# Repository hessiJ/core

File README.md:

core
========================================

A feather wing shield with ADC and highG ACC.

Repository Contents
-------------------

* **/Hardware** - Eagle design files (.brd, .sch)
* **/Firmware** - Contains the library for the microcontroller (.h, .cpp)
* **/Software** - Contains the apk library for android 

Documentation
--------------

Product Versions Hardware
----------------
* [core-feather-shield-adc-hGacc] - A feather wing shield with ADC and highG ACC.
* [core-feather-shield-adc-imu-basic_v1_0] - A feather wing shield with ADC and IMU.
* [core-feather-shield-adc-imu-basic_v2_0] - A feather wing shield with ADC and IMU.
* [core-feather-shield-adc-imu-advanced_v1_0] - A feather wing shield with multi-channel ADC and IMU.
* [core-feather-shield-adc-imu-advanced_v1_1] - A feather wing shield with multi-channel ADC and IMU.

Version History
---------------
* [V1.0.0] - Initial Release

License Information
-------------------

This product is _**open source**_! 

Please review the LICENSE.md file for license information. 

Distributed as-is; no warranty is given.

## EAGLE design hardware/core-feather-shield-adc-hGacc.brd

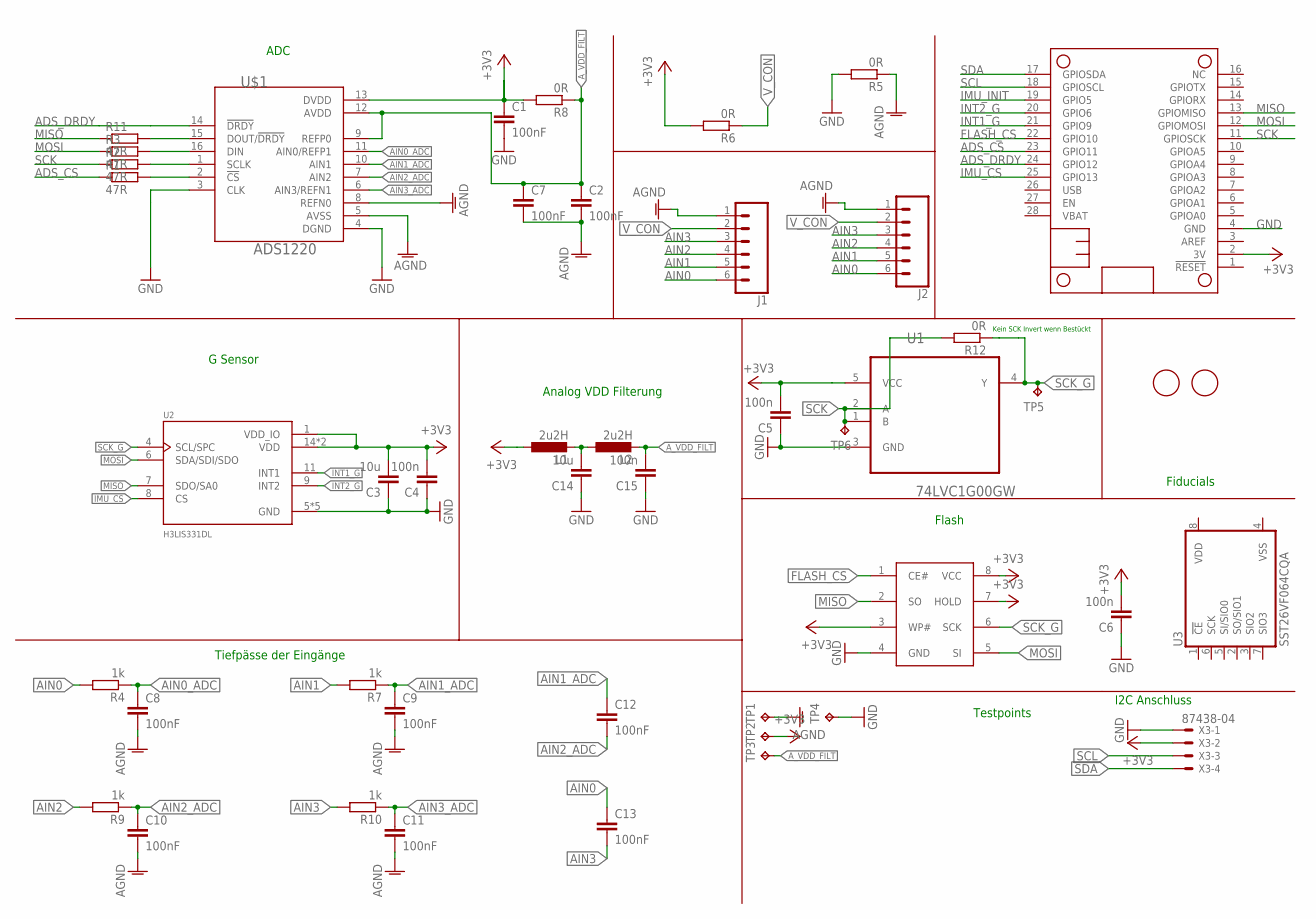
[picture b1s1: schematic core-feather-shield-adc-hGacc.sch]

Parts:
C1, C2, C7, C8, C9, C10, C11, C12, C13: 100nF; C0805
C3, C14: 10u; C0805
C4, C5, C6, C15: 100n; C0805
J1, J2: CONN_06SMD_MALE; 1X06_SMD_MALE
L1, L2: 2u2H; L0805
MS1: FEATHERWING
R1, R2, R3, R11: 47R; R0805
R4, R7, R9, R10: 1k; R0805
R5, R6, R8, R12: 0R; R0805
TP1, TP2, TP3, TP4, TP5, TP6: TPTP10R; TP10R
U1: 74LVC1G00GW; SOT65P210X110-5N
U2: H3LIS331DL; QFN300X300X100-16N
U3: SST26VF064CQA; WSON8
U$1: ADS1220; TSSOP-16
U$2: IS25LP128F-JKLE-TR; WSON-8-PAD
U$8, U$9: FIDUCIAL; FIDUCIAL_1MM
X3: 87438-04

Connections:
+3V3: C1.1, C3.2, C4.2, C5.2, C6.2, L1.1, MS1.2 (3V), R6.2, R8.2, TP2.TP, U1.5 (VCC), U2.1 (VDD_IO), U2.14 (VDD), U2.15 (VDD), U$1.13 (DVDD), U$2.3 (WP#), U$2.7 (HOLD), U$2.8 (VCC), X3.2
ADS_CS: MS1.23 (GPIO11), R1.1
ADS_DRDY: MS1.24 (GPIO12), U$1.14 (!DRDY)
AGND: C2.2, C7.2, C8.2, C9.2, C10.2, C11.2, J1.1, J2.1, R5.1, TP1.TP, U$1.5 (AVSS), U$1.8 (REFN0)
AIN0: C13.1, J1.6, J2.6, R4.2
AIN0_ADC: C8.1, R4.1, U$1.11 (AIN0/REFP1)
AIN1: J1.5, J2.5, R7.2
AIN1_ADC: C9.1, C12.1, R7.1, U$1.10 (AIN1)
AIN2: J1.4, J2.4, R9.2
AIN2_ADC: C10.1, C12.2, R9.1, U$1.7 (AIN2)
AIN3: C13.2, J1.3, J2.3, R10.2
AIN3_ADC: C11.1, R10.1, U$1.6 (AIN3/REFN1)
A_VDD_FILT: C2.1, C7.1, C15.2, L2.2, R8.1, TP3.TP, U$1.9 (REFP0), U$1.12 (AVDD)
FLASH_CS: MS1.22 (GPIO10), U$2.1 (CE#)
GND: C1.2, C3.1, C4.1, C5.1, C6.1, C14.1, C15.1, MS1.4 (GND), R5.2, TP4.TP, U1.3 (GND), U2.5 (GND), U2.10 (GND), U2.12 (GND), U2.13 (GND), U2.16 (GND), U$1.4 (DGND), U$2.4 (GND), X3.1
IMU_CS: MS1.25 (GPIO13), U2.8 (CS)
IMU_INIT: MS1.19 (GPIO5)
INT1_G: MS1.21 (GPIO9), U2.11 (INT1)
INT2_G: MS1.20 (GPIO6), U2.9 (INT2)
MISO: MS1.13 (GPIOMISO), R11.1, U2.7 (SDO/SA0), U$2.2 (SO)
MOSI: MS1.12 (GPIOMOSI), R3.1, U2.6 (SDA/SDI/SDO), U$2.5 (SI)
unnamed: R11.2, U$1.15 (DOUT/!DRDY)
unnamed: C14.2, L1.2, L2.1
unnamed: R3.2, U$1.16 (DIN)
unnamed: R2.2, U$1.1 (SCLK)
unnamed: R1.2, U$1.2 (!CS)
SCK: MS1.11 (GPIOSCK), R2.1, R12.2, TP6.TP, U1.1 (B), U1.2 (A)
SCK_G: R12.1, TP5.TP, U1.4 (Y), U2.4 (SCL/SPC), U$2.6 (SCK)
SCL: MS1.18 (GPIOSCL), X3.3
SDA: MS1.17 (GPIOSDA), X3.4
VDD: U3.8 (VDD)
VSS: U3.4 (VSS)
V_CON: J1.2, J2.2, R6.1

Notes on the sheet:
Fiducials
Kein SCK Invert wenn Bestückt
Flash
I2C Anschluss
Tiefpässe der Eingänge
G Sensor
Analog VDD Filterung
ADC
Testpoints

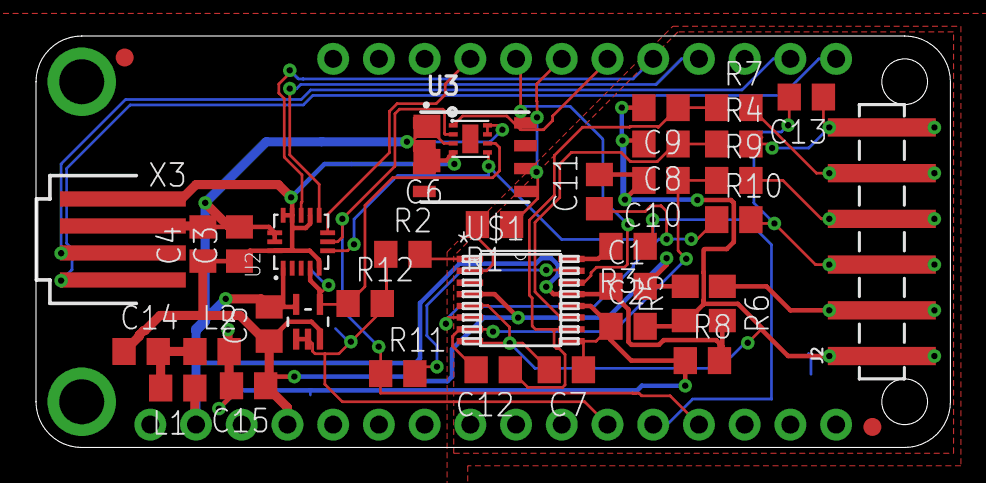
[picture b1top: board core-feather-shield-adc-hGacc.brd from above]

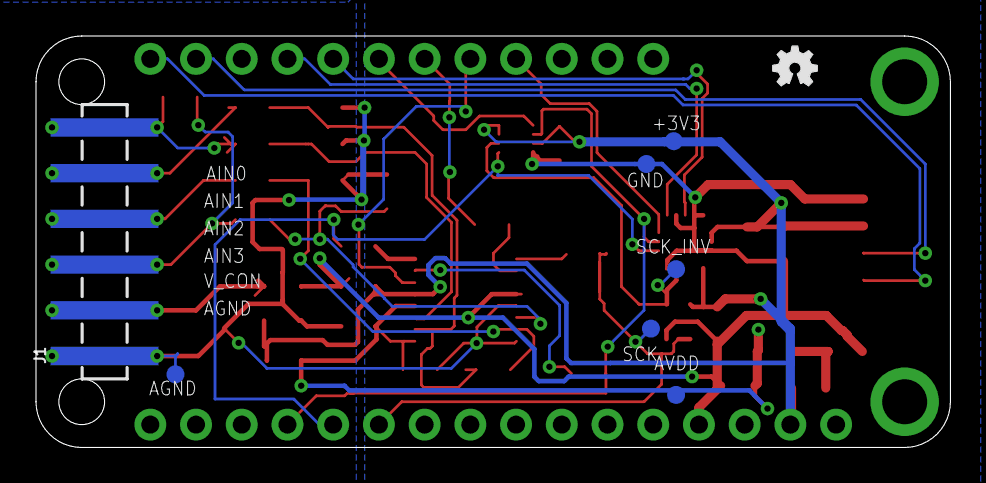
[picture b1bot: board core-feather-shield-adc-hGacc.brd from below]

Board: 2 copper layers, 50.8 x 22.9 mm, 49 parts (8 on the bottom side), 30 nets.

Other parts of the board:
FRAME2: FRAME-LETTER; CREATIVE_COMMONS
LOGO1: OSHW-LOGOMINI; OSHW-LOGO-MINI
LOGO2: REVISION

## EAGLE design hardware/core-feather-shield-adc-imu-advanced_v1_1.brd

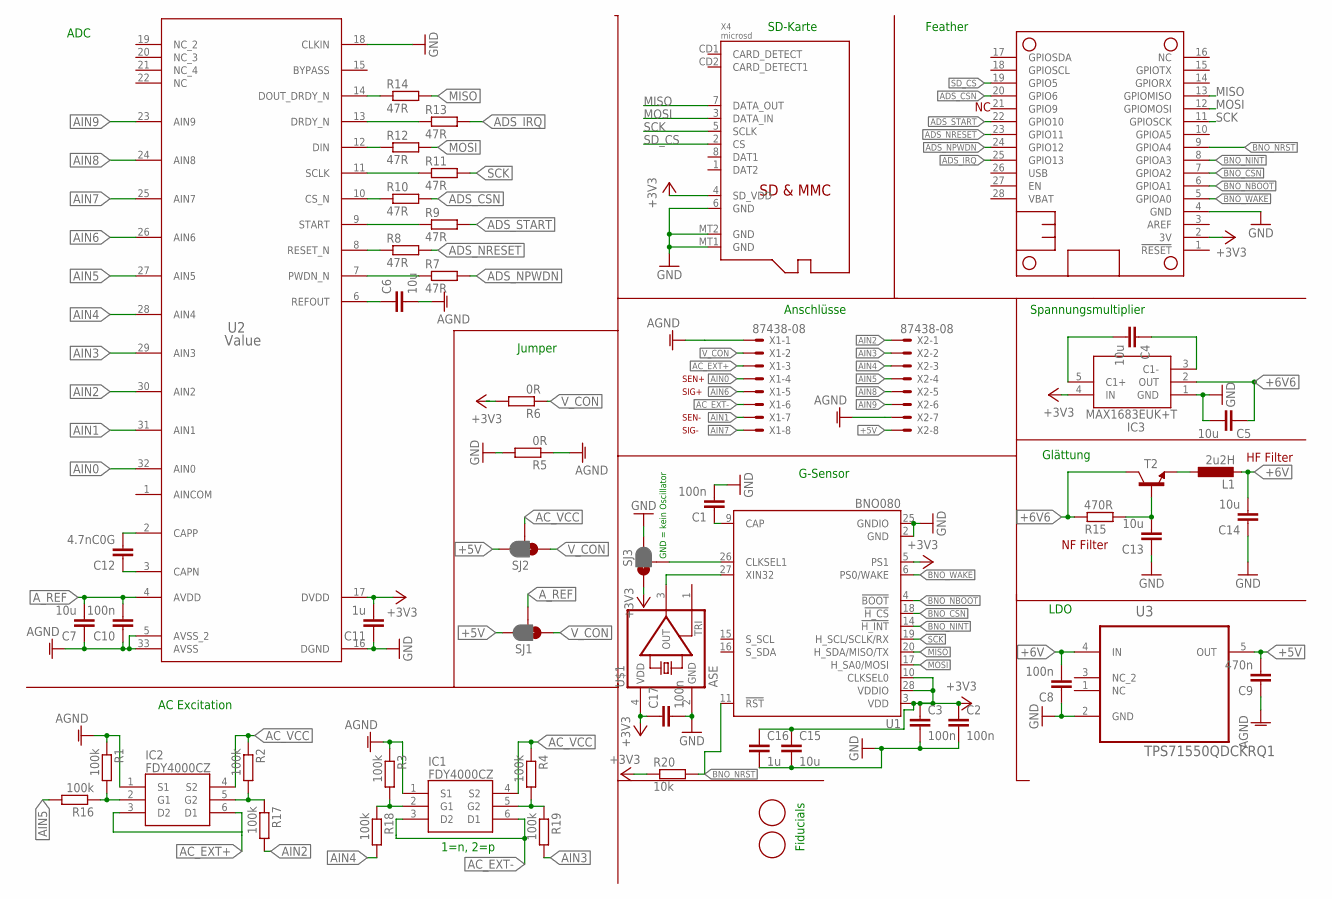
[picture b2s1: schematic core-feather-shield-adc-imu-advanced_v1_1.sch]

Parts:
C1, C2, C3, C8, C10, C17: 100n; C0805
C4, C5, C6, C7, C13, C14, C15: 10u; C0805
C9: 470n; C0805
C11, C16: 1u; C0805
C12: 4.7nC0G; C0805
IC1, IC2: FDY4000CZ; SOTFL50P160X60-6N
IC3: MAX1683EUK+T; SOT95P280X145-5N
L1: 2u2H; L0805
MS1: FEATHERWING
R1, R2, R3, R4, R16, R17, R18, R19: 100k; R0805
R5, R6: 0R; R0805
R7, R8, R9, R10, R11, R12, R13, R14: 47R; R0805
R15: 470R; R0805
R20: 10k; R0805
SJ1, SJ2, SJ3: JUMPER_PAD-3-1&2_NC_BY_PASTE; PAD-HUMPER-3-1&2_NC_BY_PASTE_YES_SILK_FULL_BOX
T2: BC808-NPN-SOT23-BEC; SOT23-BEC
U1: BNO080; LGA-28
U2: Value; RHB0032E
U3: TPS71550QDCKRQ1; SOT65P210X110-5N
U$1: ASE
U$8, U$9: FIDUCIAL; FIDUCIAL_1MM
X1, X2: 87438-08
X4: microsd; MICROSD

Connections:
+3V3: C2.1, C3.1, C11.2, C15.1, C16.1, C17.1, IC3.4 (IN), MS1.2 (3V), R6.2, R20.1, SJ3.3, U1.3 (VDD), U1.5 (PS1), U1.10 (CLKSEL0), U1.28 (VDDIO), U2.17 (DVDD), U$1.4 (VDD), X4.4 (SD_VDD)
+5V: C9.2, SJ1.1, SJ2.1, U3.5 (OUT), X2.8
+6V: C8.2, C14.2, L1.2, U3.4 (IN)
+6V6: C5.1, IC3.2 (OUT), R15.2, T2.C
AC_EXT+: IC2.3 (D2), IC2.6 (D1), X1.3
AC_EXT-: IC1.3 (D2), IC1.6 (D1), X1.6
AC_VCC: IC1.4 (S2), IC2.4 (S2), R2.1, R4.1, SJ2.2
ADS_CSN: MS1.20 (GPIO6), R10.2
ADS_IRQ: MS1.25 (GPIO13), R13.2
ADS_NPWDN: MS1.24 (GPIO12), R7.2
ADS_NRESET: MS1.23 (GPIO11), R8.2
ADS_START: MS1.22 (GPIO10), R9.2
AGND: C6.2, C7.1, C9.1, C10.1, IC1.1 (S1), IC2.1 (S1), R1.1, R3.1, R5.1, U2.5 (AVSS_2), U2.33 (AVSS), X1.1, X2.7
AIN0: U2.32 (AIN0), X1.4
AIN1: U2.31 (AIN1), X1.7
AIN2: R17.2, U2.30 (AIN2), X2.1
AIN2_P: IC2.5 (G2), R2.2, R17.1
AIN3: R19.2, U2.29 (AIN3), X2.2
AIN3_P: IC1.5 (G2), R4.2, R19.1
AIN4: R18.2, U2.28 (AIN4), X2.3
AIN4_N: IC1.2 (G1), R3.2, R18.1
AIN5: R16.2, U2.27 (AIN5), X2.4
AIN5_N: IC2.2 (G1), R1.2, R16.1
AIN6: U2.26 (AIN6), X1.5
AIN7: U2.25 (AIN7), X1.8
AIN8: U2.24 (AIN8), X2.5
AIN9: U2.23 (AIN9), X2.6
A_REF: C7.2, C10.2, SJ1.2, U2.4 (AVDD)
BNO_CSN: MS1.7 (GPIOA2), U1.18 (!H_CS)
BNO_NBOOT: MS1.6 (GPIOA1), U1.4 (!BOOT)
BNO_NINT: MS1.8 (GPIOA3), U1.14 (!H_INT)
BNO_NRST: MS1.9 (GPIOA4), R20.2, U1.11 (!RST)
BNO_WAKE: MS1.5 (GPIOA0), U1.6 (PS0/WAKE)
GND: C1.2, C2.2, C3.2, C5.2, C8.1, C11.1, C13.1, C14.1, C15.2, C16.2, C17.2, IC3.1 (GND), MS1.4 (GND), R5.2, SJ3.1, U1.2 (GND), U1.25 (GNDIO), U2.16 (DGND), U2.18 (CLKIN), U3.2 (GND), U$1.2 (GND), X4.6 (GND), X4.MT1 (GND), X4.MT2 (GND)
MISO: MS1.13 (GPIOMISO), R14.2, U1.20 (H_SDA/MISO/TX), X4.7 (DATA_OUT)
MOSI: MS1.12 (GPIOMOSI), R12.2, U1.17 (H_SA0/MOSI), X4.3 (DATA_IN)
unnamed: C1.1, U1.9 (CAP)
unnamed: C4.1, IC3.3 (C1-)
unnamed: C4.2, IC3.5 (C1+)
unnamed: C13.2, R15.1, T2.B
unnamed: L1.1, T2.E
unnamed: C6.1, U2.6 (REFOUT)
unnamed: C12.2, U2.2 (CAPP)
unnamed: C12.1, U2.3 (CAPN)
unnamed: R7.1, U2.7 (PWDN_N)
unnamed: R8.1, U2.8 (RESET_N)
unnamed: R9.1, U2.9 (START)
unnamed: R10.1, U2.10 (CS_N)
unnamed: R11.1, U2.11 (SCLK)
unnamed: R14.1, U2.14 (DOUT_DRDY_N)
unnamed: R13.1, U2.13 (DRDY_N)
unnamed: R12.1, U2.12 (DIN)
unnamed: U1.27 (XIN32), U$1.3 (OUT)
unnamed: SJ3.2, U1.26 (CLKSEL1)
SCK: MS1.11 (GPIOSCK), R11.2, U1.19 (H_SCL/SCLK/RX), X4.5 (SCLK)
SD_CS: MS1.19 (GPIO5), X4.2 (CS)
V_CON: R6.1, SJ1.3, SJ2.3, X1.2

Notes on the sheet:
Fiducials
1=n, 2=p
LDO
Spannungsmultiplier
Glättung
NF Filter
HF Filter
SEN+
SEN-
SIG+
SIG-
G-Sensor
ADC
AC Excitation
Jumper
Anschlüsse
SD-Karte
Feather
GND = kein Oscillator

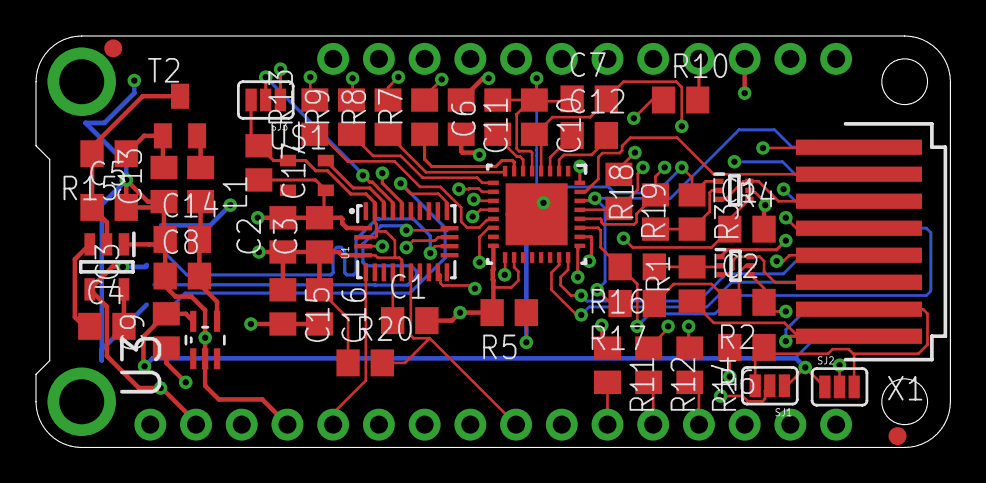
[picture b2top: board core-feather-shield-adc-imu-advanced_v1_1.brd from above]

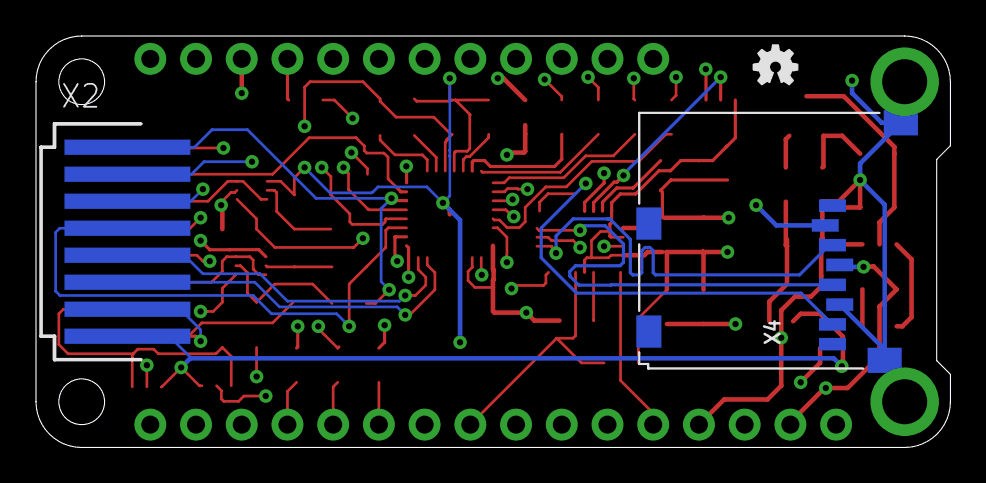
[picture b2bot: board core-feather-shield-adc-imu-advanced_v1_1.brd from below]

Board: 4 copper layers, 50.8 x 22.9 mm, 58 parts (3 on the bottom side), 57 nets.

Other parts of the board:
FRAME2: FRAME-LETTER; CREATIVE_COMMONS
LOGO1: OSHW-LOGOMINI; OSHW-LOGO-MINI
LOGO2: REVISION

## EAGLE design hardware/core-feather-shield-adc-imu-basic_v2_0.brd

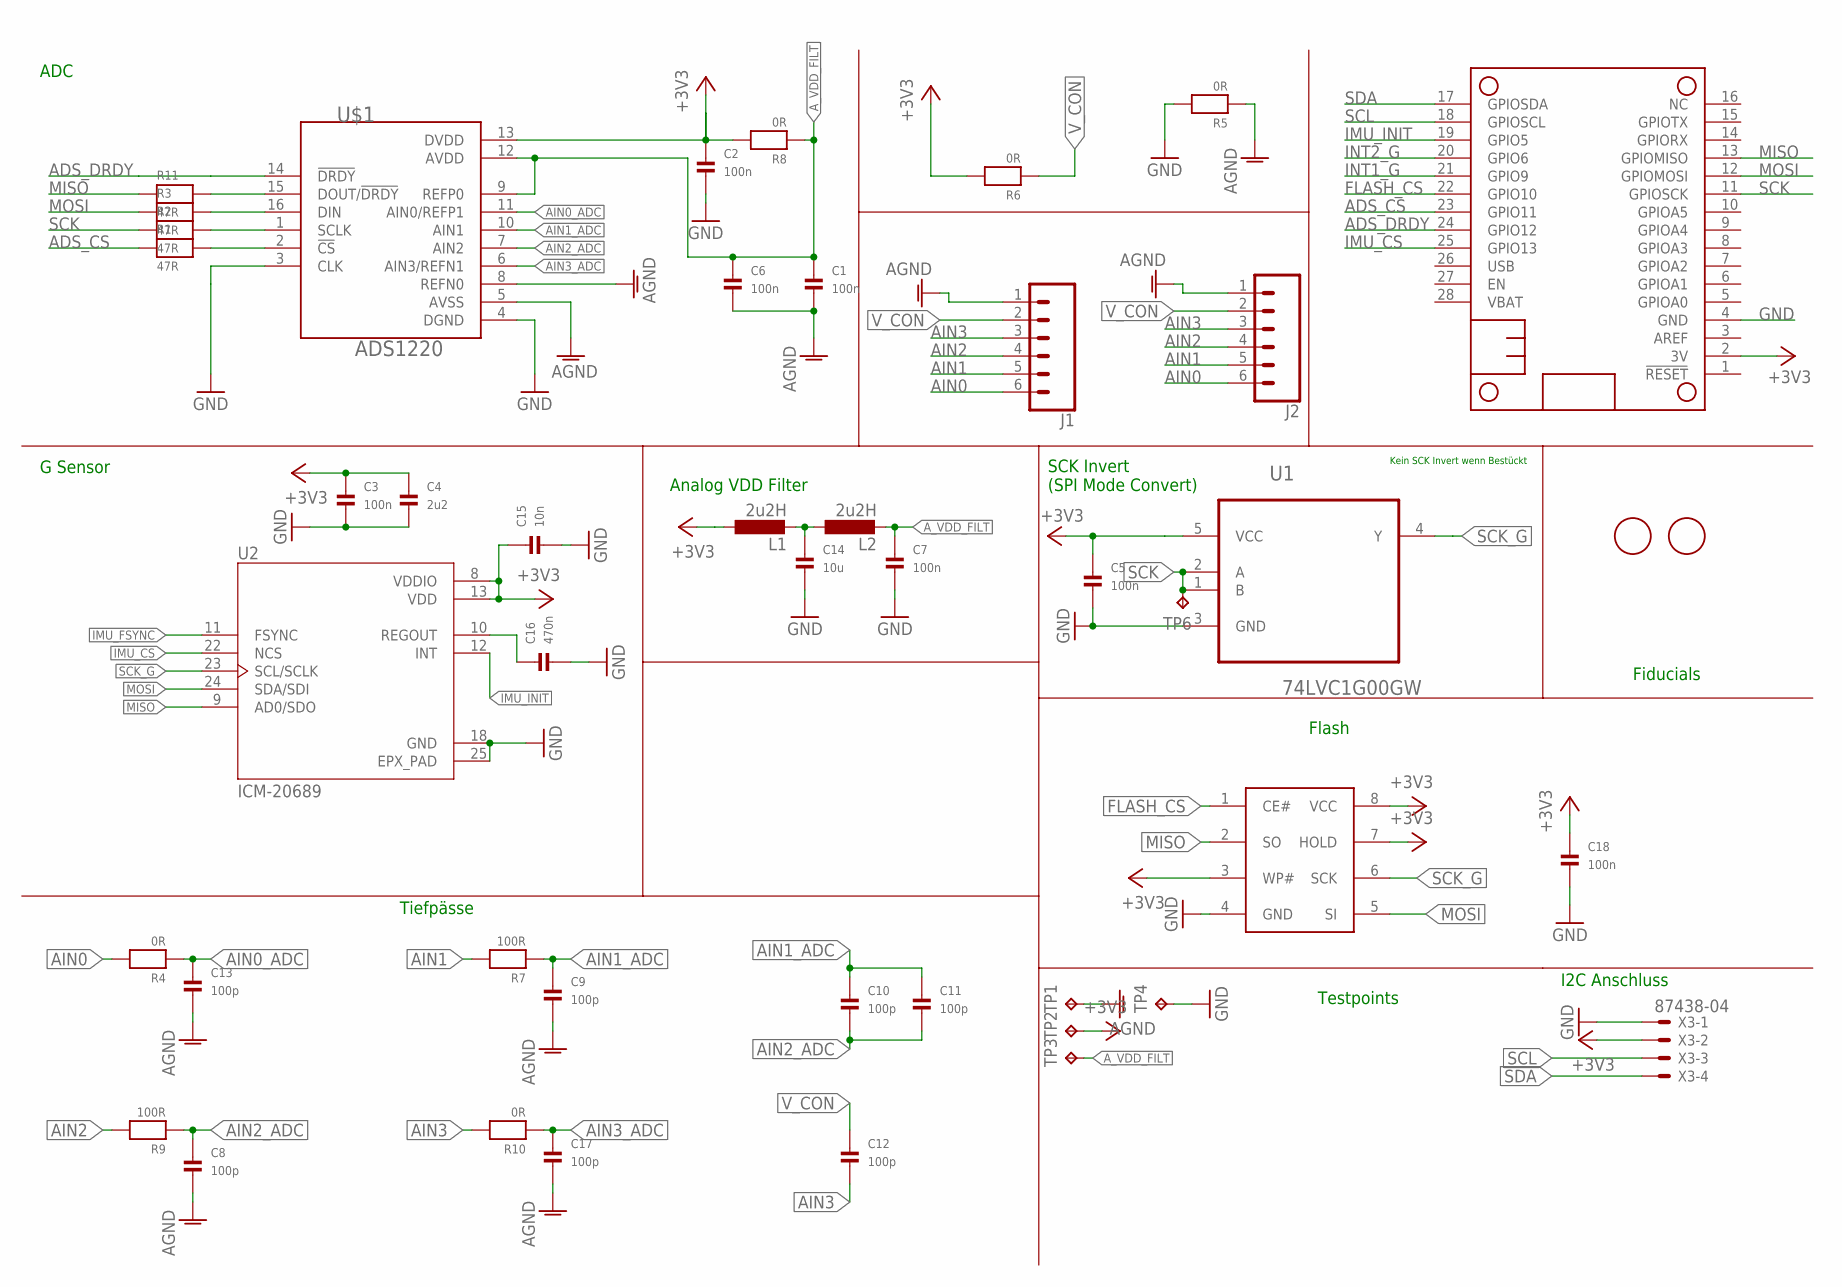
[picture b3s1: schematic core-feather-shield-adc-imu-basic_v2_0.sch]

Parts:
C1, C2, C3, C5, C6, C7, C18: 100n; 0402
C4: 2u2; 0402
C8, C9, C10, C11, C12, C13, C17: 100p; 0402
C14: 10u; 0402
C15: 10n; 0402
C16: 470n; 0402
J1, J2: CONN_06SMD_MALE; 1X06_SMD_MALE
L1, L2: 2u2H; L0805
MS1: FEATHERWING
R1, R2, R3, R11: 47R; 0402
R4, R5, R6, R8, R10: 0R; 0402
R7, R9: 100R; 0402
TP1, TP2, TP3, TP4, TP6: TPTP10R; TP10R
U1: 74LVC1G00GW; SOT65P210X110-5N
U2: ICM-20689; QFN50P400X400X95-25N
U$1: ADS1220; TSSOP-16
U$2: IS25LP128F-JKLE; WSON8
U$8, U$9: FIDUCIAL; FIDUCIAL_1MM
X3: 87438-04

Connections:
+3V3: C2.1, C3.1, C4.1, C5.1, C15.1, C18.1, L1.1, MS1.2 (3V), R6.2, R8.2, TP2.TP, U1.5 (VCC), U2.8 (VDDIO), U2.13 (VDD), U$1.13 (DVDD), U$2.3 (WP#), U$2.7 (HOLD), U$2.8 (VCC), X3.2
ADS_CS: MS1.23 (GPIO11), R1.1
ADS_DRDY: MS1.24 (GPIO12), U$1.14 (!DRDY)
AGND: C1.2, C6.2, C8.2, C9.2, C13.2, C17.2, J1.1, J2.1, R5.1, TP1.TP, U$1.5 (AVSS), U$1.8 (REFN0)
AIN0: J1.6, J2.6, R4.2
AIN0_ADC: C13.1, R4.1, U$1.11 (AIN0/REFP1)
AIN1: J1.5, J2.5, R7.2
AIN1_ADC: C9.1, C10.1, C11.1, R7.1, U$1.10 (AIN1)
AIN2: J1.4, J2.4, R9.2
AIN2_ADC: C8.1, C10.2, C11.2, R9.1, U$1.7 (AIN2)
AIN3: C12.2, J1.3, J2.3, R10.2
AIN3_ADC: C17.1, R10.1, U$1.6 (AIN3/REFN1)
A_VDD_FILT: C1.1, C6.1, C7.1, L2.2, R8.1, TP3.TP, U$1.9 (REFP0), U$1.12 (AVDD)
FLASH_CS: MS1.22 (GPIO10), U$2.1 (CE#)
GND: C2.2, C3.2, C4.2, C5.2, C7.2, C14.2, C15.2, C16.2, C18.2, MS1.4 (GND), R5.2, TP4.TP, U1.3 (GND), U2.18 (GND), U2.25 (EPX_PAD), U$1.4 (DGND), U$2.4 (GND), X3.1
IMU_CS: MS1.25 (GPIO13), U2.22 (NCS)
IMU_FSYNC: U2.11 (FSYNC)
IMU_INIT: MS1.19 (GPIO5), U2.12 (INT)
INT1_G: MS1.21 (GPIO9)
INT2_G: MS1.20 (GPIO6)
MISO: MS1.13 (GPIOMISO), R11.1, U2.9 (AD0/SDO), U$2.2 (SO)
MOSI: MS1.12 (GPIOMOSI), R3.1, U2.24 (SDA/SDI), U$2.5 (SI)
unnamed: R11.2, U$1.15 (DOUT/!DRDY)
unnamed: C14.1, L1.2, L2.1
unnamed: R3.2, U$1.16 (DIN)
unnamed: R2.2, U$1.1 (SCLK)
unnamed: R1.2, U$1.2 (!CS)
unnamed: C16.1, U2.10 (REGOUT)
SCK: MS1.11 (GPIOSCK), R2.1, TP6.TP, U1.1 (B), U1.2 (A)
SCK_G: U1.4 (Y), U2.23 (SCL/SCLK), U$2.6 (SCK)
SCL: MS1.18 (GPIOSCL), X3.3
SDA: MS1.17 (GPIOSDA), X3.4
V_CON: C12.1, J1.2, J2.2, R6.1

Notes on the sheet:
Fiducials
Kein SCK Invert wenn Bestückt
Flash
I2C Anschluss
Tiefpässe
G Sensor
Analog VDD Filter
Testpoints
SCK Invert (SPI Mode Convert)
ADC

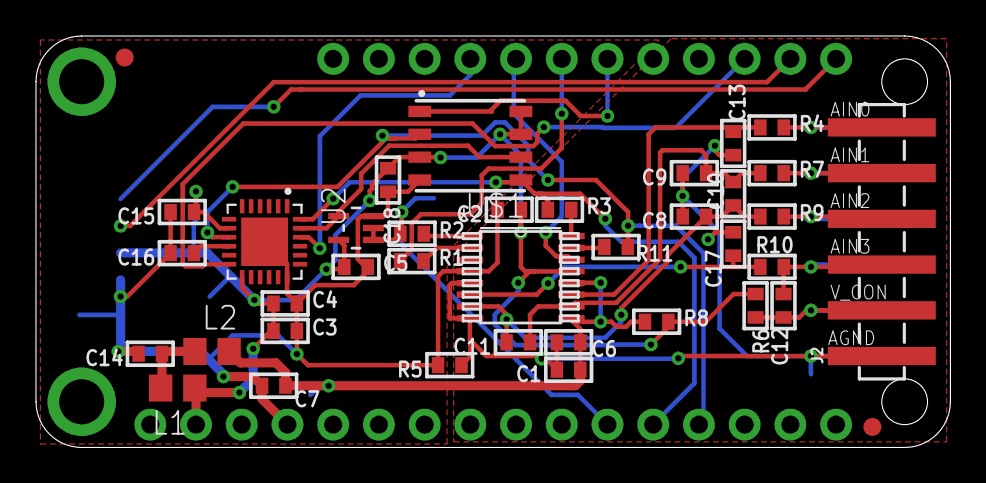
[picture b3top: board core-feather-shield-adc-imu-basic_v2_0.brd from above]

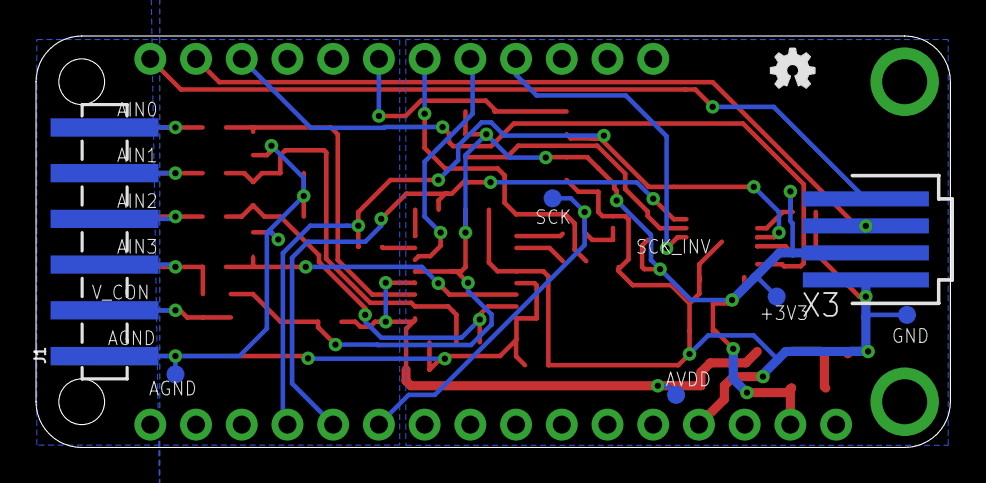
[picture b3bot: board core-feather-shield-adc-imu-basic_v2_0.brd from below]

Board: 2 copper layers, 50.8 x 22.9 mm, 49 parts (8 on the bottom side), 30 nets.

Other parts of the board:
FRAME2: FRAME-LETTER; CREATIVE_COMMONS
LOGO1: OSHW-LOGOMINI; OSHW-LOGO-MINI
LOGO2: REVISION

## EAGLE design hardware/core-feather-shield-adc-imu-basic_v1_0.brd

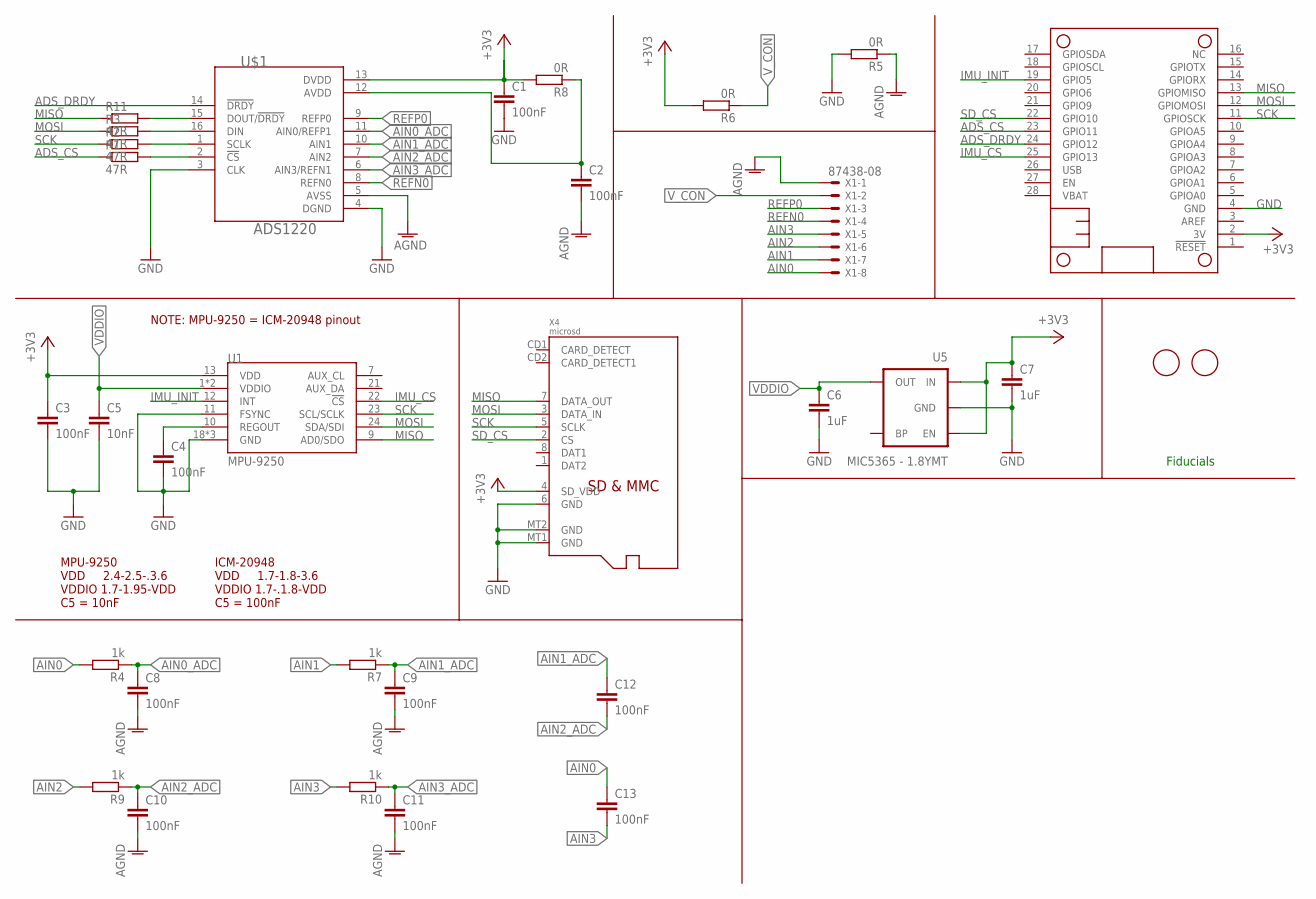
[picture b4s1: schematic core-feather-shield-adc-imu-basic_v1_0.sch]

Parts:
C1, C2, C3, C4, C8, C9, C10, C11, C12, C13: 100nF; C0805
C5: 10nF; C0805
C6, C7: 1uF; C0805
MS1: FEATHERWING
R1, R2, R3, R11: 47R; R0805
R4, R7, R9, R10: 1k; R0805
R5, R6, R8: 0R; R0805
U1: MPU-9250; QFN24_PAD
U5: MIC5365 - 1.8YMT; SC70
U$1: ADS1220; TSSOP-16
U$8, U$9: FIDUCIAL; FIDUCIAL_1MM
X1: 87438-08
X4: microsd; MICROSD

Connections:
+3V3: C1.1, C3.1, C7.1, MS1.2 (3V), R6.2, R8.2, U1.13 (VDD), U5.1 (IN), U5.3 (EN), U$1.13 (DVDD), X4.4 (SD_VDD)
ADS_CS: MS1.23 (GPIO11), R1.1
ADS_DRDY: MS1.24 (GPIO12), U$1.14 (!DRDY)
AGND: C2.2, C8.2, C9.2, C10.2, C11.2, R5.1, U$1.5 (AVSS), X1.1
AIN0: C13.1, R4.2, X1.8
AIN0_ADC: C8.1, R4.1, U$1.11 (AIN0/REFP1)
AIN1: R7.2, X1.7
AIN1_ADC: C9.1, C12.1, R7.1, U$1.10 (AIN1)
AIN2: R9.2, X1.6
AIN2_ADC: C10.1, C12.2, R9.1, U$1.7 (AIN2)
AIN3: C13.2, R10.2, X1.5
AIN3_ADC: C11.1, R10.1, U$1.6 (AIN3/REFN1)
GND: C1.2, C3.2, C4.2, C5.2, C6.2, C7.2, MS1.4 (GND), R5.2, U1.11 (FSYNC), U1.18 (GND), U1.20 (GND), U1.CENTER (GND), U5.2 (GND), U$1.4 (DGND), X4.6 (GND), X4.MT1 (GND), X4.MT2 (GND)
IMU_CS: MS1.25 (GPIO13), U1.22 (!CS)
IMU_INIT: MS1.19 (GPIO5), U1.12 (INT)
MISO: MS1.13 (GPIOMISO), R11.1, U1.9 (AD0/SDO), X4.7 (DATA_OUT)
MOSI: MS1.12 (GPIOMOSI), R3.1, U1.24 (SDA/SDI), X4.3 (DATA_IN)
unnamed: R11.2, U$1.15 (DOUT/!DRDY)
unnamed: R3.2, U$1.16 (DIN)
unnamed: R2.2, U$1.1 (SCLK)
unnamed: R1.2, U$1.2 (!CS)
unnamed: C2.1, R8.1, U$1.12 (AVDD)
REFN0: U$1.8 (REFN0), X1.4
REFP0: U$1.9 (REFP0), X1.3
REGOUT: C4.1, U1.10 (REGOUT)
SCK: MS1.11 (GPIOSCK), R2.1, U1.23 (SCL/SCLK), X4.5 (SCLK)
SD_CS: MS1.22 (GPIO10), X4.2 (CS)
VDDIO: C5.1, C6.1, U1.1 (VDDIO), U1.8 (VDDIO), U5.5 (OUT)
V_CON: R6.1, X1.2

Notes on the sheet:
NOTE: MPU-9250 = ICM-20948 pinout
MPU-9250 VDD 2.4-2.5-.3.6 VDDIO 1.7-1.95-VDD C5 = 10nF
ICM-20948 VDD 1.7-1.8-3.6 VDDIO 1.7-.1.8-VDD C5 = 100nF
Fiducials

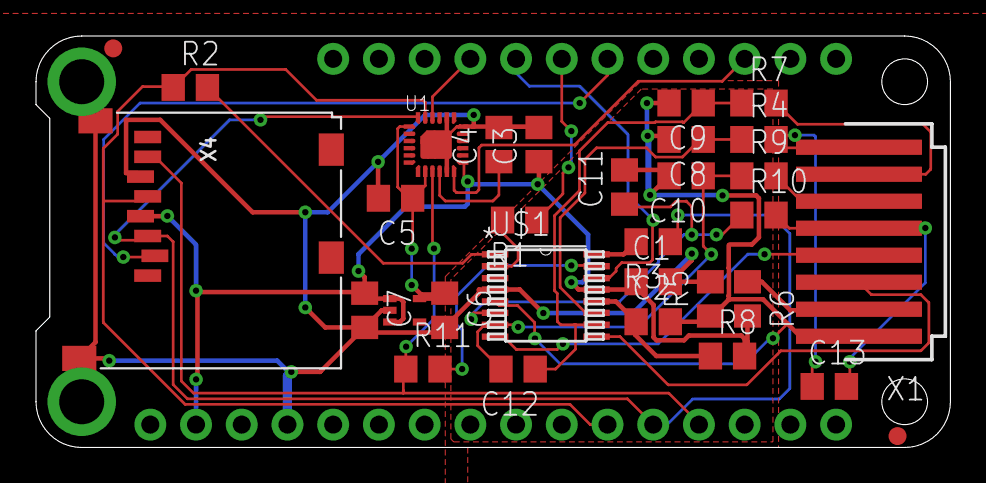
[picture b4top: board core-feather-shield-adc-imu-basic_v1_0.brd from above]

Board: 2 copper layers, 50.8 x 22.9 mm, 35 parts (1 on the bottom side), 29 nets.

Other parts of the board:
FRAME2: FRAME-LETTER; CREATIVE_COMMONS
LOGO1: OSHW-LOGOMINI; OSHW-LOGO-MINI
LOGO2: REVISION

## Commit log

2019-11-08 files uploaded
2019-11-08 file upload

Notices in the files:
parts and their libraries:
SparkFun-Connectors: Licensing: Creative Commons ShareAlike 4.0 International - https://creativecommons.org/licenses/by-sa/4.0
SparkFun-Aesthetics: Licensing: CC v3.0 Share-Alike You are welcome to use this library for commercial purposes.
